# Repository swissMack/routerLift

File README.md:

# routerLift

Open-firmware automated router lift for a workshop router table. A 4.3" touch
panel with a CNC-style handwheel drives a stepper-actuated lift body, with
motion handled by stock [FluidNC](https://github.com/bdring/FluidNC).

Specification: `docs/Router_Lift_Requirement_Specification_RevG.md`, amended by
the Rev H design set.

## Architecture — two boards

Motion and the operator interface run on separate controllers. FluidNC does not
run on the ESP32-S3, and the S3 board cannot carry the machine's full pin
budget, so one board cannot do both.

```
  ESP32-S3 touch panel                 classic ESP32
  ┌──────────────────┐   UART/GRBL   ┌──────────────────┐
  │  hmi/  (our C++) │ ────────────► │ stock FluidNC    │   TB6600 ─► stepper
  │  LVGL, handwheel │ ◄──────────── │ firmware/*.yaml  │   NPN limits, probe
  └──────────────────┘  status @10Hz └──────────────────┘   relay ─► router
```

The HMI polls status with `?` every 100 ms — FluidNC's automatic report only
fires on change. No status for 500 ms counts as link loss: the HMI sends a feed
hold and invalidates Z0.

**The HMI has no motion authority.** Soft limits, hard limits, homing and
probing are all enforced by FluidNC. A bug in our firmware can produce a *wrong
cutting depth*; it must never produce an *unsafe move*. Keeping FluidNC stock
means the safety-critical parts are not ours to get wrong — any proposal that
needs FluidNC source edits forfeits that.

| Directory | Contents |
| --- | --- |
| `firmware/` | FluidNC machine definition — `config.yaml` only, **no source** |
| `hmi/` | PlatformIO ESP32-S3 project: LVGL UI, handwheel, buttons, GRBL sender |
| `legacy/` | The retired v1.x single-ESP32 firmware. Reference only, not built |
| `docs/` | Spec, Rev H design set, wiring, protocol, bench tests, mechanics |

## Hardware

**Motion board** — classic ESP32 (30-pin USB-C ESP32-WROOM-32 devkit) running
unmodified FluidNC v4.1.0. TB6600 driver at 1/8 microstepping (1600 pulse/rev),
24–36 V, common anode +3.3 V, 1.0–1.4 A/phase. NPN NC inductive limit switches,
`G38.2` probe for tool zeroing, `Relay` spindle output for router power with a
2500 ms spin-up gate. Host lift: sauter FML-P (1.5 mm lead, 65 mm travel).

**Operator panel** — Guition JC4827W543C board (XH-S3E N4R8 module: ESP32-S3,
4 MB flash, 8 MB octal PSRAM). 4.3" 480×272 IPS NV3041A panel over QSPI via
Arduino_GFX, GT911 capacitive touch, LVGL 8.4. The board brings only ten GPIOs
out to connectors, so the panel buttons and the rough/fine selector sit on an
MCP23017 on its own I²C bus (GPIO 15/16) — the touch bus is not brought out.
MPG handwheel decoded on the S3's PCNT peripheral (GPIO 6/7), through a 74LVC14
on 3.3 V (two stages per channel, non-inverting).

STOP is deliberately *not* on the panel: it is wired to FluidNC's own
`feed_hold_pin`, so it halts motion even if the HMI has crashed.

Full pin map and wiring: `docs/HARDWARE.md`, `docs/WIRING-RevH.svg`,
`docs/SCHEMATIC-RevH.svg`, `docs/PINOUT.svg`.

## Status

Bench truth lives in `docs/BRINGUP-LOG.md`. As of 2026-09-13:

| Half | State |
| --- | --- |
| Motion board | ✅ FluidNC v4.1.0 flashed, `config.yaml` parses, bare-board acceptance passed (limits NC-correct). Five items still to verify — `firmware/README.md` |
| Screen board | ✅ Display and touch working on the JC4827W543C |
| UART link (Step B) | ✅ Link up, link-loss feed hold + Z0 invalidation, recovery verified |
| `hmi/` increments 1–3 | Built. Display, touch and link bench-verified; MPG and buttons **not yet wired** (waiting on the level shifters) |
| `hmi/` increment 4 | Cycles (standard → bit-change → dovetail → keyhole). Not started |
| `hmi/` increment 5 | Fault log, diagnostics, runtime hours. Not started |
| Mechanics | Lift body (sauter FML-P) **not yet bought**. See `docs/MECHANICS-RevH.md` |

HMI flash use is ~24% of the 3 MB app slot.

### Nothing has been cut yet

Two numbers come from the sauter FML-P datasheet, not a measurement, and both
follow from its 1.5 mm screw lead:

- `firmware/config.yaml` → `steps_per_mm: 1066.67` (1600 pulse/rev ÷ 1.5 mm),
  with `max_travel_mm: 65`
- `hmi/include/config.h` → `MpgCfg::SCREW_LEAD_MM = 1.5`

**Until `steps_per_mm` is measured against a dial indicator, every depth this
machine cuts is wrong by an unknown factor** — and wrong invisibly, because
there is no stall detection to contradict a bad number. The commissioning
procedure is in `firmware/README.md`.

One design question is also open: the foot switch needs both press and release
edges for dead-man behaviour, and FluidNC's `macro0_pin` may only fire on
assert. The proposed split (press on FluidNC, release mirrored to an HMI
expander input) is written up in `firmware/README.md` and not yet verified.

## Build

Only the HMI is built from this repo. FluidNC is flashed from its own release.

```sh
git clone git@github.com:swissMack/routerLift.git
cd routerLift
pio run -e hmi           # compile
pio run -e hmi -t upload # flash the S3 panel
pio run -e hmi-diag      # bring-up diagnostics build (no I2C, display logging)
pio device monitor       # serial console at 115200
```

Libraries resolve on first build: ESP32Encoder, GFX Library for Arduino, LVGL
8.4, TAMC_GT911. If upload cannot connect because the app has hung, hold BOOT,
tap RST and retry.

For the motion board, flash stock FluidNC from installer.fluidnc.com, upload
`firmware/config.yaml` with `$Xmodem/Receive=/localfs/config.yaml`, and restart
with `$Bye` — see `firmware/README.md`. Its console is also reachable over WiFi:
`telnet routerlift.local 23`.

## Documentation

| File | Contents |
| --- | --- |
| [docs/Router_Lift_Requirement_Specification_RevG.md](docs/Router_Lift_Requirement_Specification_RevG.md) | The requirement spec |
| [docs/DESIGN-PLAN-RevH.md](docs/DESIGN-PLAN-RevH.md) | The RevG pivot, phase by phase |
| [docs/UART-PROTOCOL.md](docs/UART-PROTOCOL.md) | HMI ↔ FluidNC command vocabulary |
| [docs/MECHANICS-RevH.md](docs/MECHANICS-RevH.md) | Lift body selection and stepper drive design |
| [docs/LIFT-COMPARISON.md](docs/LIFT-COMPARISON.md) | The four candidate lift bodies, compared |
| [docs/BOM.md](docs/BOM.md) | Bill of materials |
| [docs/HARDWARE.md](docs/HARDWARE.md) | Pin map and wiring detail |
| [docs/BENCH-TEST.md](docs/BENCH-TEST.md) | Staged bring-up — each step passes before the next part is fitted |
| [docs/BRINGUP-LOG.md](docs/BRINGUP-LOG.md) | What has actually been proven on the bench, session by session |
| [docs/UX.md](docs/UX.md) | Interaction model |
| [docs/DESIGN-QA.md](docs/DESIGN-QA.md) | The design Q&A that settled the constants |
| [hmi/README.md](hmi/README.md) | HMI modules, build gotchas, Z0 validity rules |
| [firmware/README.md](firmware/README.md) | FluidNC setup, pre-power-up checks, commissioning |
| [CHANGELOG.md](CHANGELOG.md) | Version history |
| [CONTRIBUTING.md](CONTRIBUTING.md) | Code style, commit conventions |

`docs/SUPERSEDED.md` lists the drawings the Rev H set replaced.
`docs/reference/FXBB-original/` holds the FXBB FräsLift V3 documentation this
project draws on.

## Safety

This machine drives a high-RPM router. Read `firmware/README.md` before first
power-up — five of its checks are destructive or silently wrong if got wrong,
including PSU voltage (48 V destroys the TB6600), TB6600 common anode at 3.3 V
not 5 V, and NPN-not-PNP limit sensors.

Z0 — the reference every cut depth is measured from — is owned entirely by the
HMI, and **there is no override anywhere** on probe validity. That is
deliberate: a wrong reference does not fail visibly, it produces a
plausible-looking cut at the wrong depth. See `hmi/README.md`.

The author accepts no liability for misuse. Test with the router unpowered
first.

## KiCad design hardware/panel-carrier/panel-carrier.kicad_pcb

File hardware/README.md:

# Hardware — KiCad schematics (Rev H)

Generated from Python. **Do not edit the `.kicad_sch` files in KiCad** — the next
regeneration overwrites them. Change `tools/*.py` and run:

    hardware/tools/verify.sh     # tests, generate, ERC, PDFs, pin cross-check

After running `verify.sh`, restore unchanged PDFs with `git checkout -- hardware/*/*.pdf` unless the schematics actually changed.

| Project | What | For layout? |
| --- | --- | --- |
| `motion-carrier/` | ESP32 devkit sockets, 5 input conditioners, field terminals, link header | Yes |
| `panel-carrier/` | 74LVC14 MPG shifter, MCP23017 + pull-ups, MX1.25 leads to the display | Yes |
| `system/` | Mains, E-stop, PSU, modules and cabling between them | No — reference |

`tools/check_pins.py` fails if a schematic pin disagrees with `firmware/config.yaml` or
`hmi/include/pins.h`.

## PCBs

Boards are generated once, then **the routed `.kicad_pcb` is the source** — edit it in KiCad's PCB
Editor freely. Rebuilding from scratch overwrites hand edits:

    hardware/tools/get_freerouting.sh                                   # once
    /Applications/KiCad/KiCad.app/Contents/Frameworks/Python.framework/Versions/Current/bin/python3 \
      hardware/tools/gen_pcb.py motion-carrier                          # or panel-carrier

`get_freerouting.sh` fetches v2.1.0, which runs on Java 21. `gen_pcb.py` uses only the jar for
that pinned version (`hardware/tools/.cache/freerouting-2.1.0.jar`) and stops with an error if it
is missing. To try another version, delete the cached jar first, then run e.g.
`FREEROUTING_VERSION=v2.4.1 hardware/tools/get_freerouting.sh` — and run `gen_pcb.py` with the same
`FREEROUTING_VERSION` set. v2.2 and later need Java 25.

**Regenerating a board is destructive.** It overwrites the `.kicad_pcb`, replaces the `board` and
`net_settings` sections of its `.kicad_pro` (design rules and net classes edited in the GUI are
discarded; other sections are kept), and rewrites the fab zip, the board PDF and the renders.

`verify.sh` and `gen_pcb.py` run DRC with schematic parity and `--severity-all`, so warnings fail
too. Autorouting gives a different result each run, so check DRC after every regeneration.
Fabrication zips for JLCPCB (2-layer, 1.6 mm, HASL) are in `<board>/fab/<board>-jlcpcb.zip`.

| Board | Size | Mounting |
| --- | --- | --- |
| motion carrier | 140 × 80 mm | 4× M3 for standard DIN-rail PCB clips |
| panel carrier | 80 × 62 mm | 4× M3 corners, standoffs |

Mounting hole centres, in mm from the board's top-left corner (x right, y down). Each board's holes
form a rectangle:

| Board | Holes (x, y) | Pitch (x × y) |
| --- | --- | --- |
| motion carrier | (4, 4), (93, 4), (4, 56.5), (93, 56.5) | 89 × 52.5 mm |
| panel carrier | (4, 4), (76, 4), (4, 58), (76, 58) | 72 × 54 mm |

## Open items shown on the drawings

- Contactor coil voltage (BOM block A).
- MPG output type — R3/R4 on the panel carrier are DNP until known.
- Foot-switch release mirror (MCP GPA6) — needs a second pedal contact or a shared-contact decision.
- ESP32 devkit row spacing assumed 25.4 mm — measure before ordering boards.
- DIN-rail clip hole spacing — check against the clips bought.

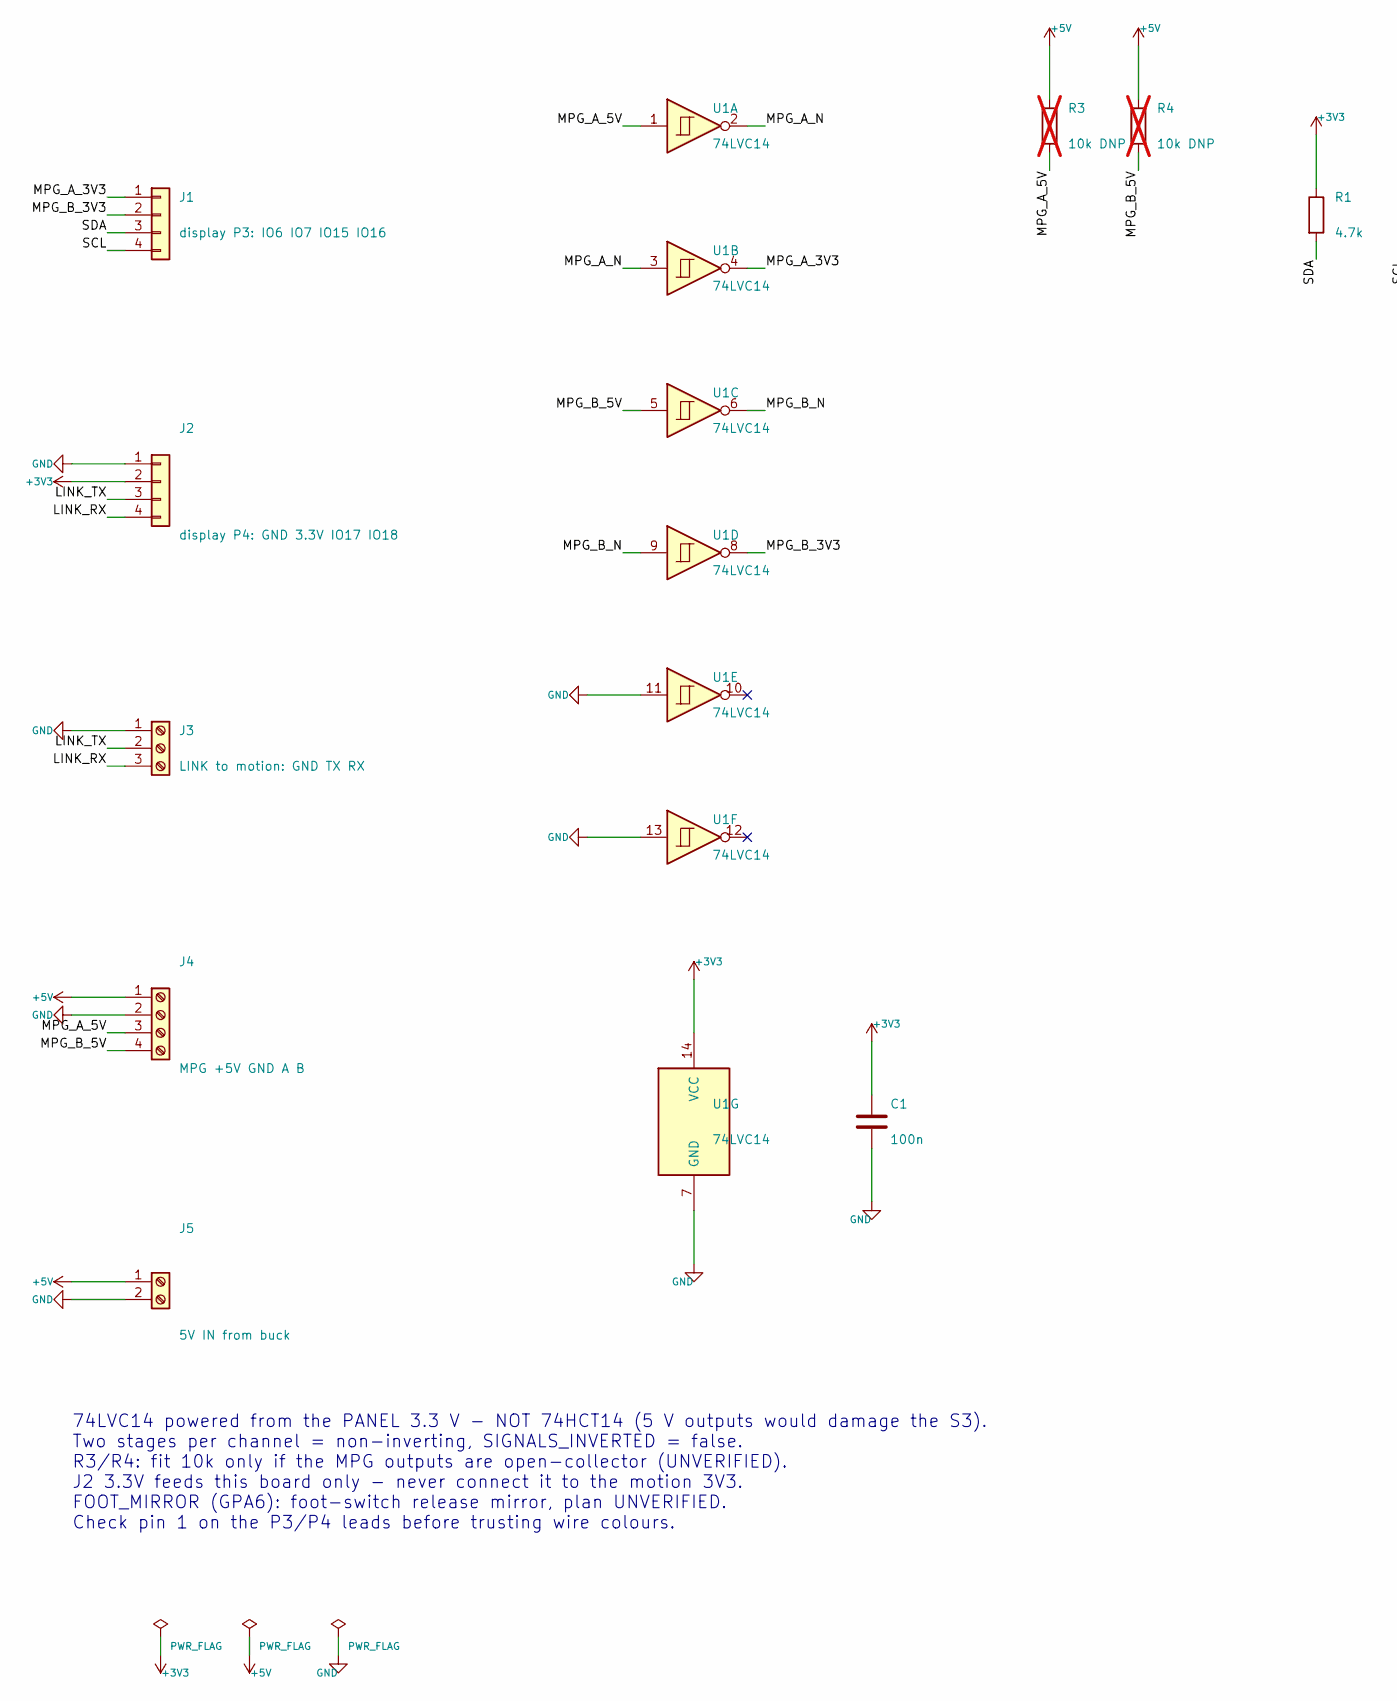
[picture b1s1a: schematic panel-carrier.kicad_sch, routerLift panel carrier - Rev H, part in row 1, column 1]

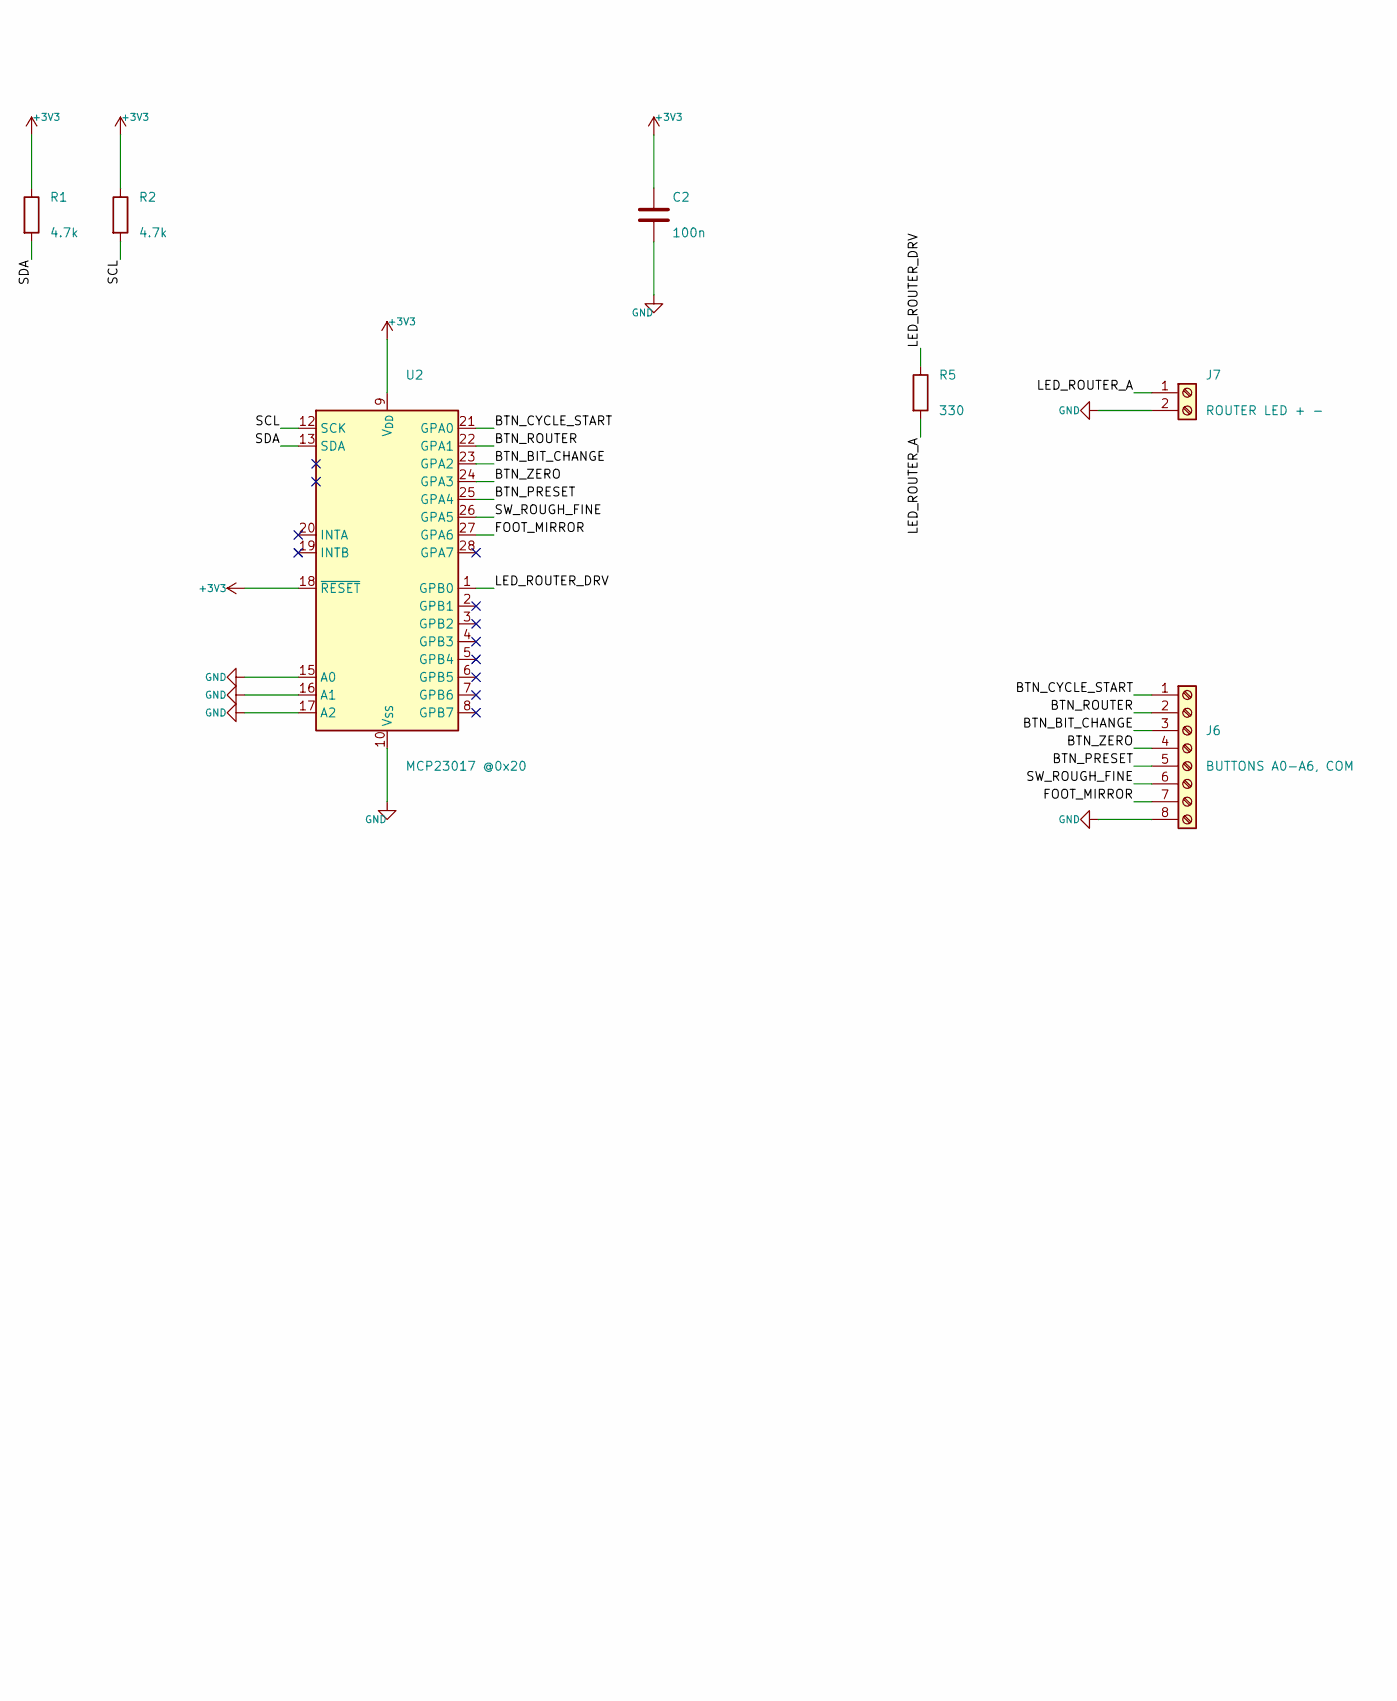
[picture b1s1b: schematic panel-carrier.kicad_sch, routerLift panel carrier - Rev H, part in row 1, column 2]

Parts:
C1, C2: 100n; C_Disc_D5.0mm_W2.5mm_P5.00mm
J1: display P3: IO6 IO7 IO15 IO16; Molex_PicoBlade_53047-0410_1x04_P1.25mm_Vertical
J2: display P4: GND 3.3V IO17 IO18; Molex_PicoBlade_53047-0410_1x04_P1.25mm_Vertical
J3: LINK to motion: GND TX RX; TerminalBlock_Phoenix_MKDS-1,5-3-5.08_1x03_P5.08mm_Horizont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
J4: MPG +5V GND A B; TerminalBlock_Phoenix_MKDS-1,5-4-5.08_1x04_P5.08mm_Horizont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
J5: 5V IN from buck; TerminalBlock_Phoenix_MKDS-1,5-2-5.08_1x02_P5.08mm_Horizont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
J6: BUTTONS A0-A6, COM; TerminalBlock_Phoenix_MKDS-1,5-8-5.08_1x08_P5.08mm_Horizont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
J7: ROUTER LED + -; TerminalBlock_Phoenix_MKDS-1,5-2-5.08_1x02_P5.08mm_Horizont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
R1, R2: 4.7k; R_Axial_DIN0207_L6.3mm_D2.5mm_P7.62mm_Horizontal
R3, R4: 10k DNP; R_Axial_DIN0207_L6.3mm_D2.5mm_P7.62mm_Horizontal; not fitted
R5: 330; R_Axial_DIN0207_L6.3mm_D2.5mm_P7.62mm_Horizontal
U1: 74LVC14; SOIC-14_3.9x8.7mm_P1.27mm
U2: MCP23017 @0x20; SOIC-28W_7.5x17.9mm_P1.27mm

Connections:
+3V3: C1.1, C2.1, J2.2, R1.1, R2.1, U1.14 (VCC), U2.9 (V_{DD}), U2.18 (~RESET)
+5V: J4.1, J5.1, R3.1, R4.1
/BTN_BIT_CHANGE: J6.3, U2.23 (GPA2)
/BTN_CYCLE_START: J6.1, U2.21 (GPA0)
/BTN_PRESET: J6.5, U2.25 (GPA4)
/BTN_ROUTER: J6.2, U2.22 (GPA1)
/BTN_ZERO: J6.4, U2.24 (GPA3)
/FOOT_MIRROR: J6.7, U2.27 (GPA6)
/LED_ROUTER_A: J7.1, R5.2
/LED_ROUTER_DRV: R5.1, U2.1 (GPB0)
/LINK_RX: J2.4, J3.3
/LINK_TX: J2.3, J3.2
/MPG_A_3V3: J1.1, U1.4
/MPG_A_5V: J4.3, R3.2, U1.1
/MPG_A_N: U1.2, U1.3
/MPG_B_3V3: J1.2, U1.8
/MPG_B_5V: J4.4, R4.2, U1.5
/MPG_B_N: U1.6, U1.9
/SCL: J1.4, R2.2, U2.12 (SCK)
/SDA: J1.3, R1.2, U2.13 (SDA)
/SW_ROUGH_FINE: J6.6, U2.26 (GPA5)
GND: C1.2, C2.2, J2.1, J3.1, J4.2, J5.2, J6.8, J7.2, U1.7 (GND), U1.11, U1.13, U2.10 (V_{SS}), U2.15 (A0), U2.16 (A1), U2.17 (A2)

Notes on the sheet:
74LVC14 powered from the PANEL 3.3 V - NOT 74HCT14 (5 V outputs would damage the S3). Two stages per channel = non-inverting, SIGNALS_INVERTED = false. R3/R4: fit 10k only if the MPG outputs are open-collector (UNVERIFIED). J2 3.3V feeds this board only - never connect it to the motion 3V3. FOOT_MI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

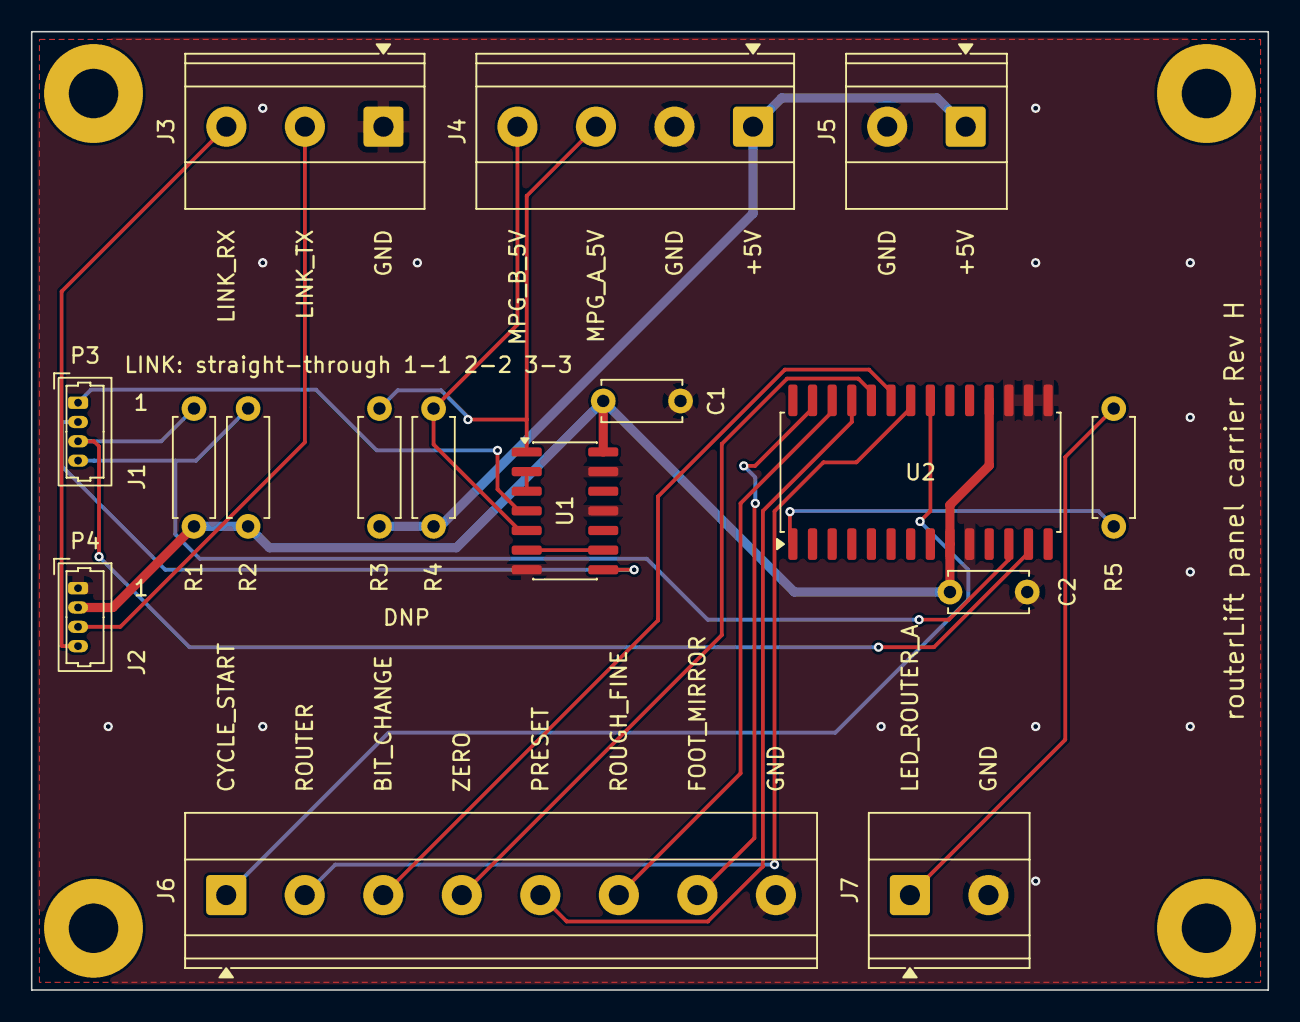
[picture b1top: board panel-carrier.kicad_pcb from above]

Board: 2 copper layers, 80.0 x 62.0 mm, 20 parts (0 on the bottom side), 22 nets.

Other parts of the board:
H1, H2, H3, H4: M3; MountingHole_3.2mm_M3_Pad

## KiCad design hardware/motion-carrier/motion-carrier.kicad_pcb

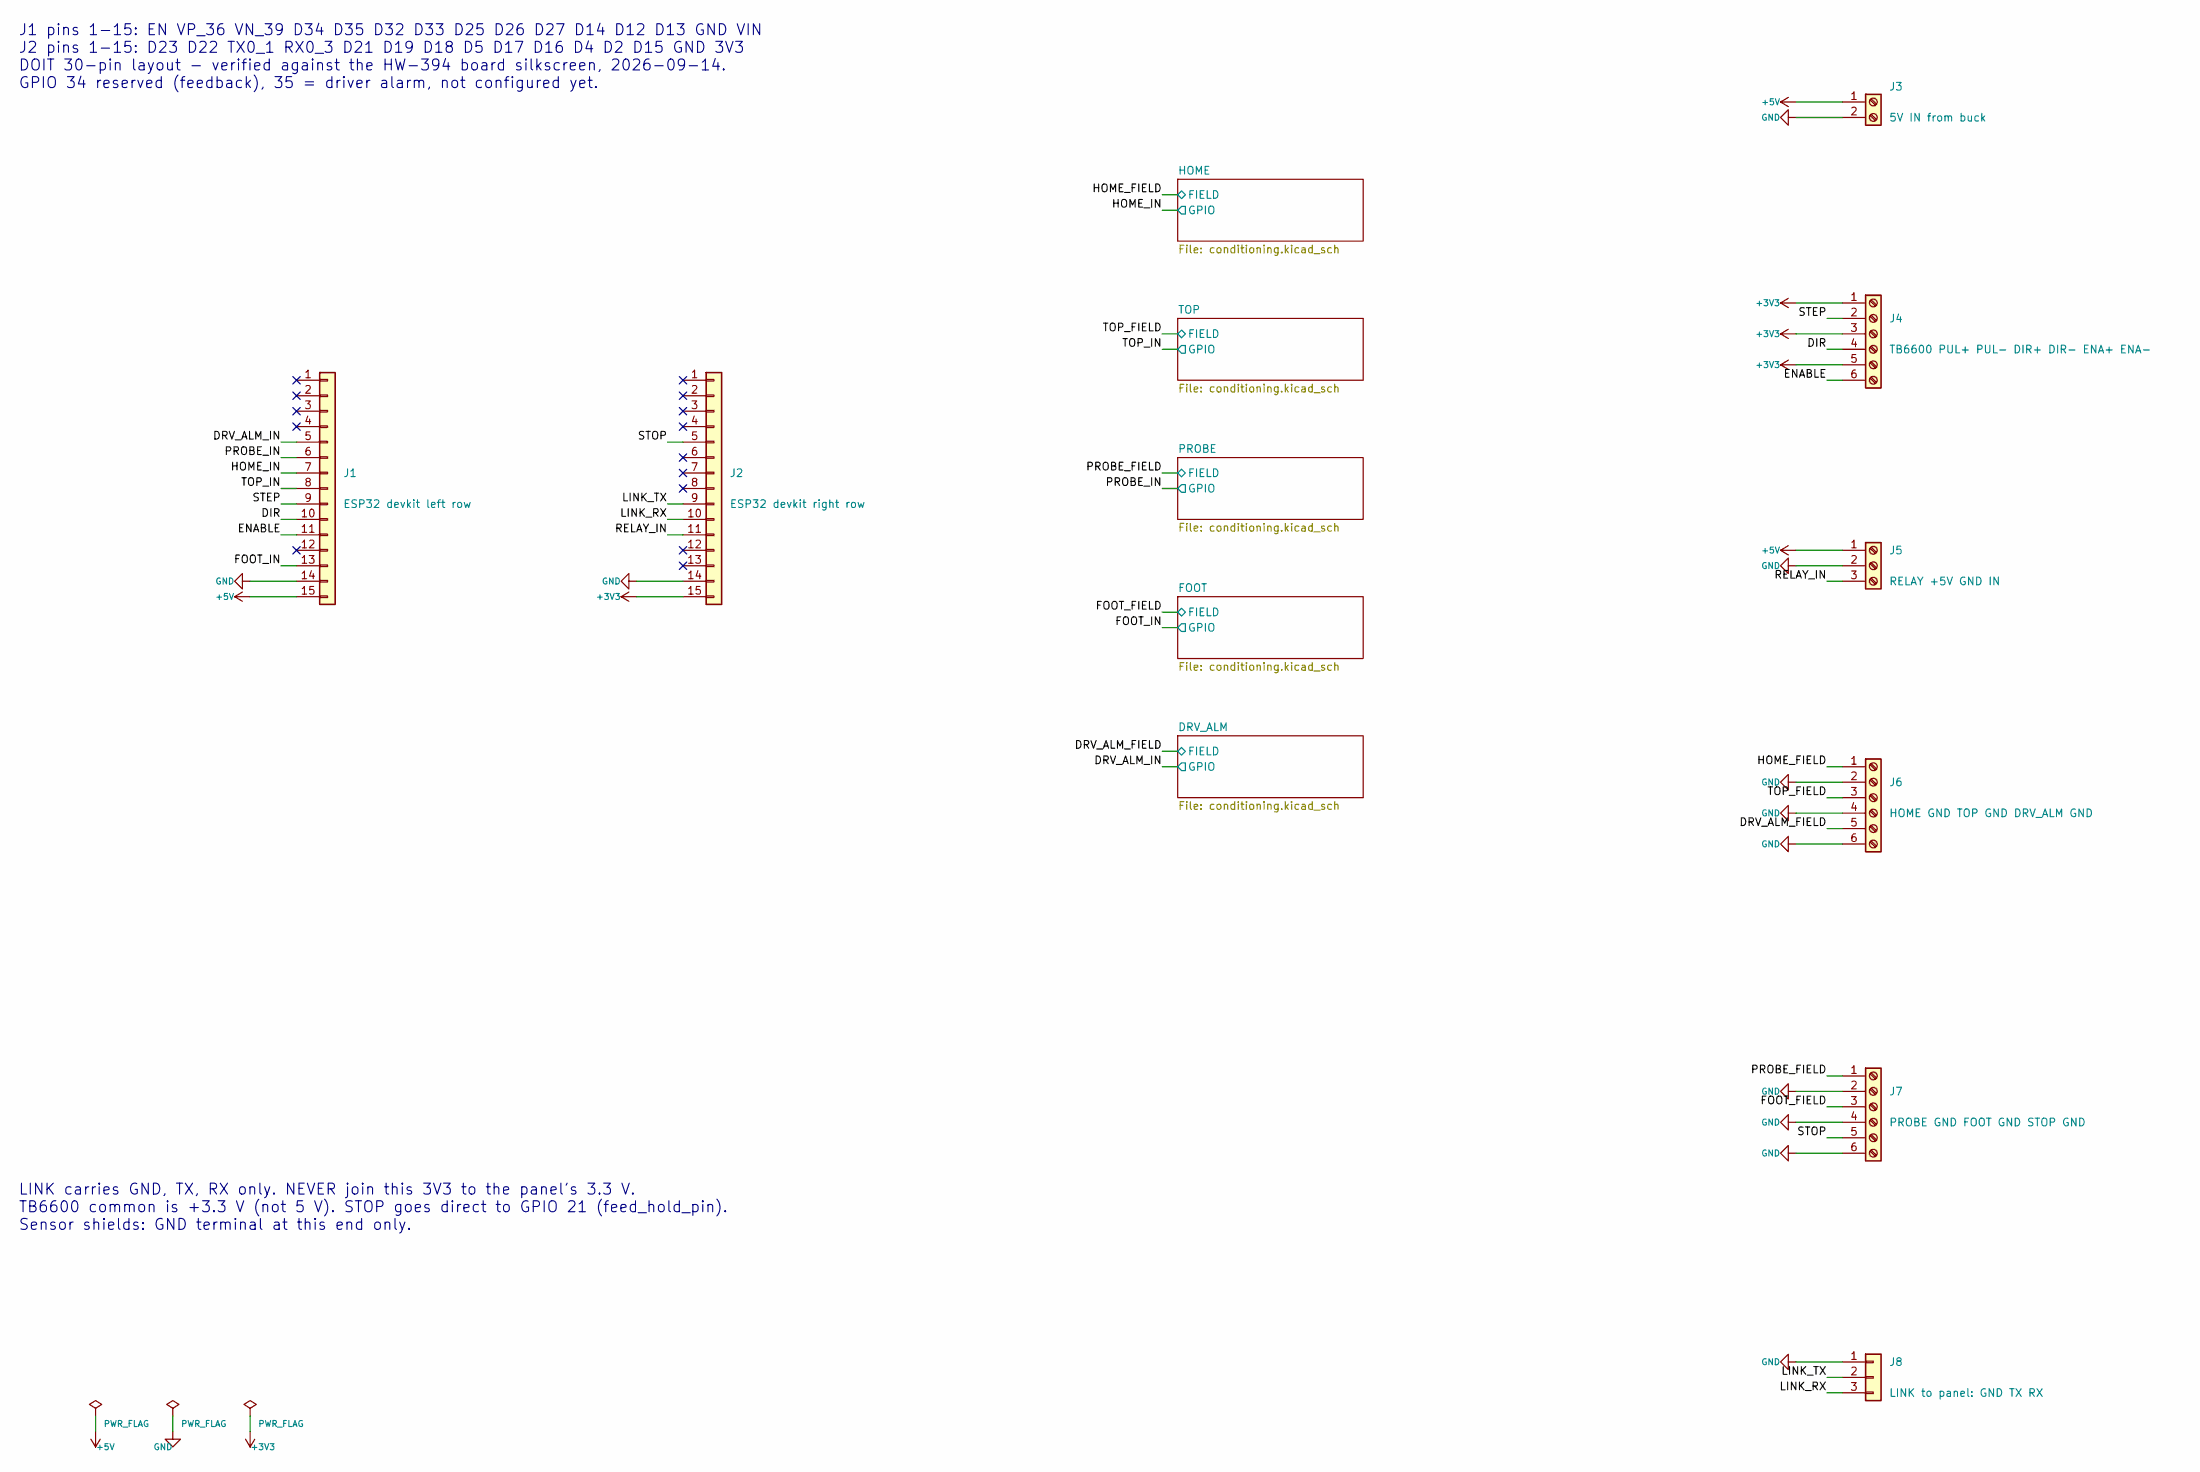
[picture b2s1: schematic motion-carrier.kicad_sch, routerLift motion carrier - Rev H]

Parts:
J1: ESP32 devkit left row; PinSocket_1x15_P2.54mm_Vertical
J2: ESP32 devkit right row; PinSocket_1x15_P2.54mm_Vertical
J3: 5V IN from buck; TerminalBlock_Phoenix_MKDS-1,5-2-5.08_1x02_P5.08mm_Horizont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
J4: TB6600 PUL+ PUL- DIR+ DIR- ENA+ ENA-; TerminalBlock_Phoenix_MKDS-1,5-6-5.08_1x06_P5.08mm_Horizont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
J5: RELAY +5V GND IN; TerminalBlock_Phoenix_MKDS-1,5-3-5.08_1x03_P5.08mm_Horizont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
J6: HOME GND TOP GND DRV_ALM GND; TerminalBlock_Phoenix_MKDS-1,5-6-5.08_1x06_P5.08mm_Horizont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
J7: PROBE GND FOOT GND STOP GND; TerminalBlock_Phoenix_MKDS-1,5-6-5.08_1x06_P5.08mm_Horizont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
J8: LINK to panel: GND TX RX; JST_XH_B3B-XH-A_1x03_P2.50mm_Vertical

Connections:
+3V3: J2.15, J4.1, J4.3, J4.5; also elsewhere on the board
+5V: J1.15, J3.1, J5.1
/DIR: J1.10, J4.4
/DRV_ALM_FIELD: J6.5; also elsewhere on the board
/DRV_ALM_IN: J1.5; also elsewhere on the board
/ENABLE: J1.11, J4.6
/FOOT_FIELD: J7.3; also elsewhere on the board
/FOOT_IN: J1.13; also elsewhere on the board
/HOME_FIELD: J6.1; also elsewhere on the board
/HOME_IN: J1.7; also elsewhere on the board
/LINK_RX: J2.10, J8.3
/LINK_TX: J2.9, J8.2
/PROBE_FIELD: J7.1; also elsewhere on the board
/PROBE_IN: J1.6; also elsewhere on the board
/RELAY_IN: J2.11, J5.3
/STEP: J1.9, J4.2
/STOP: J2.5, J7.5
/TOP_FIELD: J6.3; also elsewhere on the board
/TOP_IN: J1.8; also elsewhere on the board
GND: J1.14, J2.14, J3.2, J5.2, J6.2, J6.4, J6.6, J7.2, J7.4, J7.6, J8.1; also elsewhere on the board

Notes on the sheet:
J1 pins 1-15: EN VP_36 VN_39 D34 D35 D32 D33 D25 D26 D27 D14 D12 D13 GND VIN J2 pins 1-15: D23 D22 TX0_1 RX0_3 D21 D19 D18 D5 D17 D16 D4 D2 D15 GND 3V3 DOIT 30-pin layout - verified against the HW-394 board silkscreen, 2026-09-14. GPIO 34 reserved (feedback), 35 = driver alarm, not configured yet.
LINK carries GND, TX, RX only. NEVER join this 3V3 to the panel's 3.3 V. TB6600 common is +3.3 V (not 5 V). STOP goes direct to GPIO 21 (feed_hold_pin). Sensor shields: GND terminal at this end only.

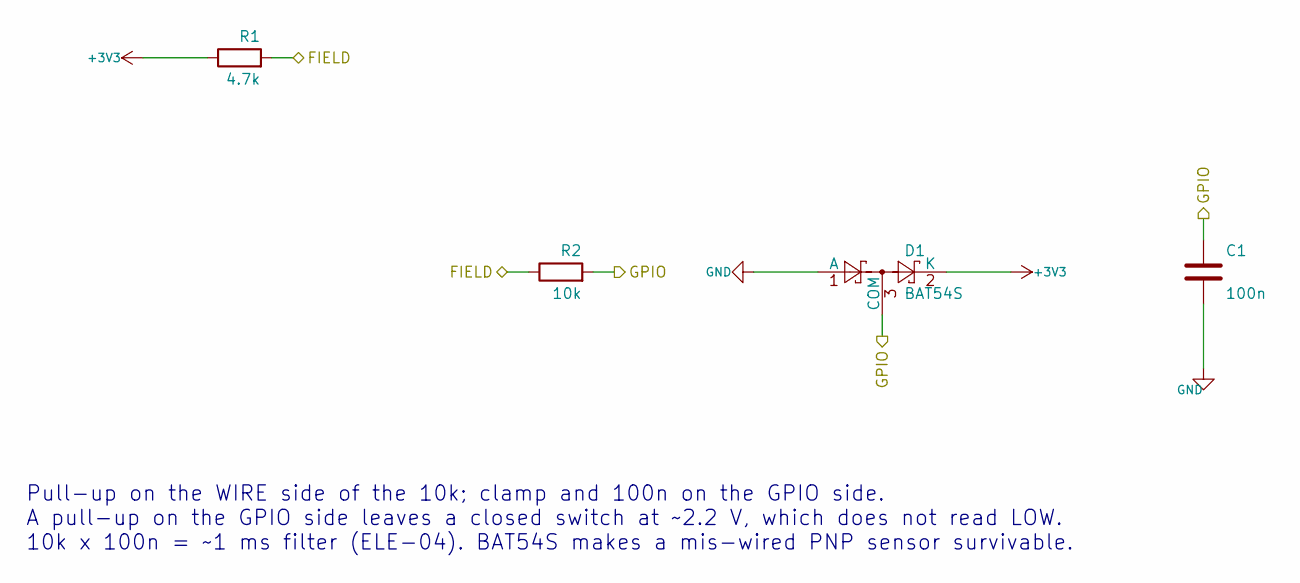
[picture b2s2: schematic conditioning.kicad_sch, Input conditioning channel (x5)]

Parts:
C1: 100n; C_Disc_D5.0mm_W2.5mm_P5.00mm
D1: BAT54S; SOT-23
R1: 4.7k; R_Axial_DIN0207_L6.3mm_D2.5mm_P7.62mm_Horizontal
R2: 10k; R_Axial_DIN0207_L6.3mm_D2.5mm_P7.62mm_Horizontal

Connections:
+3V3: D1.2 (K), R1.1; also elsewhere on the board
/HOME_FIELD: R1.2, R2.1; also elsewhere on the board
/HOME_IN: C1.1, D1.3 (COM), R2.2; also elsewhere on the board
GND: C1.2, D1.1 (A); also elsewhere on the board

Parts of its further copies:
C2, C3, C4, C5: 100n; C_Disc_D5.0mm_W2.5mm_P5.00mm
D2, D3, D4, D5: BAT54S; SOT-23
R3, R5, R7, R9: 4.7k; R_Axial_DIN0207_L6.3mm_D2.5mm_P7.62mm_Horizontal
R4, R6, R8, R10: 10k; R_Axial_DIN0207_L6.3mm_D2.5mm_P7.62mm_Horizontal

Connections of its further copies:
+3V3: D2.2 (K), D3.2 (K), D4.2 (K), D5.2 (K), R3.1, R5.1, R7.1, R9.1; also elsewhere on the board
/DRV_ALM_FIELD: R9.2, R10.1; also elsewhere on the board
/DRV_ALM_IN: C5.1, D5.3 (COM), R10.2; also elsewhere on the board
/FOOT_FIELD: R7.2, R8.1; also elsewhere on the board
/FOOT_IN: C4.1, D4.3 (COM), R8.2; also elsewhere on the board
/PROBE_FIELD: R5.2, R6.1; also elsewhere on the board
/PROBE_IN: C3.1, D3.3 (COM), R6.2; also elsewhere on the board
/TOP_FIELD: R3.2, R4.1; also elsewhere on the board
/TOP_IN: C2.1, D2.3 (COM), R4.2; also elsewhere on the board
GND: C2.2, C3.2, C4.2, C5.2, D2.1 (A), D3.1 (A), D4.1 (A), D5.1 (A); also elsewhere on the board

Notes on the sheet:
Pull-up on the WIRE side of the 10k; clamp and 100n on the GPIO side. A pull-up on the GPIO side leaves a closed switch at ~2.2 V, which does not read LOW. 10k x 100n = ~1 ms filter (ELE-04). BAT54S makes a mis-wired PNP sensor survivable.

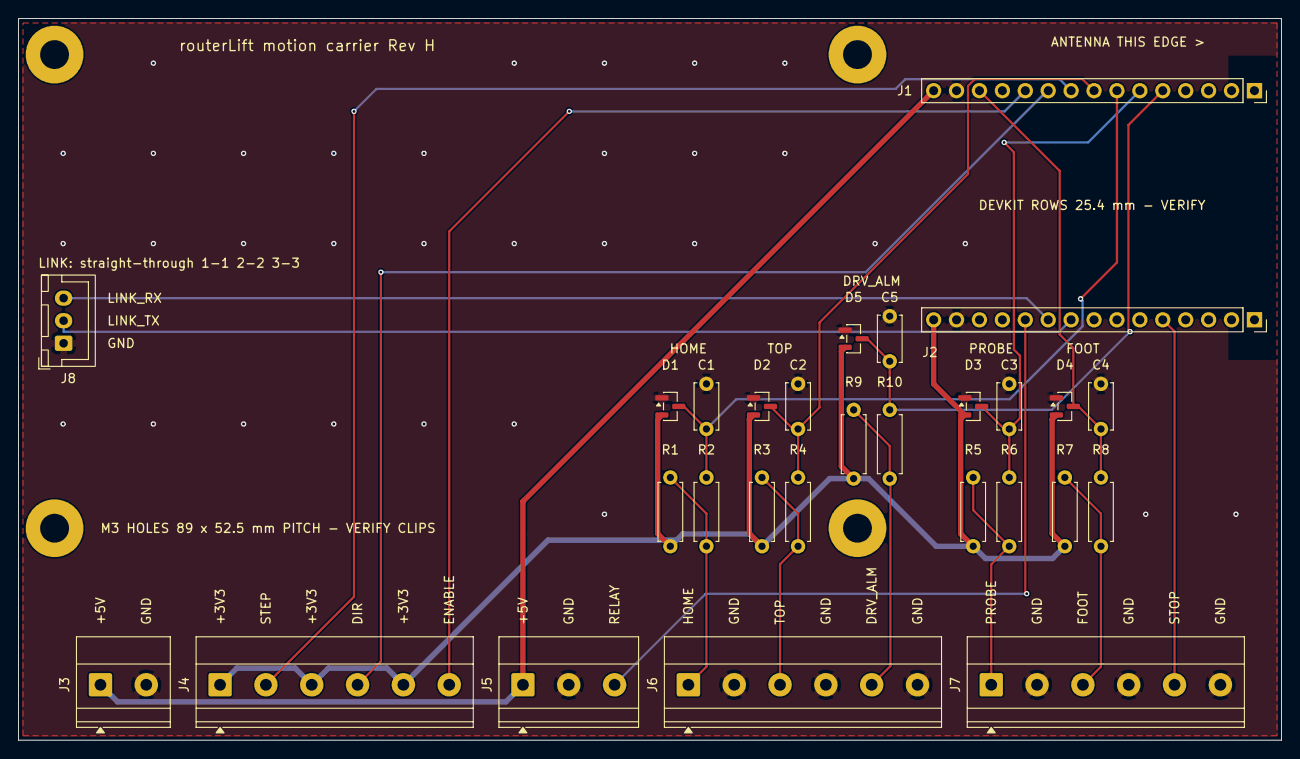
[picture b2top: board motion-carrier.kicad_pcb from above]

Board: 2 copper layers, 140.0 x 80.0 mm, 32 parts (0 on the bottom side), 20 nets.

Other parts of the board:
H1, H2, H3, H4: M3; MountingHole_3.2mm_M3_Pad

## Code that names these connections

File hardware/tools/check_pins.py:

"""Cross-check the carrier schematics against the firmware pin maps.

python3 hardware/tools/check_pins.py   (exit 0 = consistent)
"""
import os
import re
import subprocess
import sys
import tempfile
from pathlib import Path

sys.path.insert(0, str(Path(__file__).resolve().parent))
from devkit import DEVKIT_LEFT, DEVKIT_RIGHT, devkit_gpio
from kisch import find, findall, parse

KICAD_CLI = os.environ.get("KICAD_CLI", "/Applications/KiCad/KiCad.app/Contents/MacOS/kicad-cli")
HW = Path(__file__).resolve().parents[1]
REPO = HW.parent

MOTION_EXPECT = {
    ("uart1", "txd_pin"): "LINK_TX", ("uart1", "rxd_pin"): "LINK_RX",
    ("axes", "step_pin"): "STEP", ("axes", "direction_pin"): "DIR",
    ("axes", "disable_pin"): "ENABLE", ("axes", "limit_neg_pin"): "HOME_IN",
    ("axes", "limit_pos_pin"): "TOP_IN", ("probe", "pin"): "PROBE_IN",
    ("control", "feed_hold_pin"): "STOP", ("control", "macro0_pin"): "FOOT_IN",
    ("Relay", "output_pin"): "RELAY_IN",
}
RESERVED = {35: "DRV_ALM_IN"}
P3 = {"1": 6, "2": 7, "3": 15, "4": 16}
P4 = {"3": 17, "4": 18}
P4_POWER = {"1": "GND", "2": "+3V3"}
PANEL_EXPECT = {"MPG_A": "MPG_A_3V3", "MPG_B": "MPG_B_3V3", "MCP_SDA": "SDA", "MCP_SCL": "SCL",
                "UART_RX": "LINK_TX", "UART_TX": "LINK_RX"}
EXPANDER_EXPECT = {"A_CYCLE_START": "BTN_CYCLE_START", "A_ROUTER": "BTN_ROUTER",
                   "A_BIT_CHANGE": "BTN_BIT_CHANGE", "A_ZERO": "BTN_ZERO",
                   "A_PRESET": "BTN_PRESET", "A_ROUGH_FINE": "SW_ROUGH_FINE",
                   "A_FOOT_MIRROR": "FOOT_MIRROR", "B_ROUTER_LED": "LED_ROUTER_DRV"}
# GND, LINK_TX, LINK_RX in that pin order - motion-carrier J8 and panel-carrier J3 are
# the two ends of the same 3-wire link cable, so pin 1 on one end must be pin 1's net
# on the other, etc. (docs/WIRING-RevH.md, UART-PROTOCOL.md).
LINK_ORDER = ["GND", "LINK_TX", "LINK_RX"]
# GPA7 is the expander's only fully-spare button input (panel_carrier.py's mcp dict
# maps it to None -> a no-connect flag) - it must actually be unconnected in the
# schematic, not silently reused for something else.
EXPANDER_UNUSED = {"GPA7"}


def config_pins(text):
    section, out = None, {}
    for line in text.splitlines():
        if not line.strip() or line.lstrip().startswith("#"):
            continue
        m = re.match(r"^(\w+):", line)
        if m:
            section = m.group(1)
        m = re.match(r"^\s*(\w+):\s*gpio\.(\d+)", line)
        if m:
            key = (section, m.group(1))
            if key in out:
                raise ValueError("config.yaml: duplicate key %s.%s" % key)
            out[key] = int(m.group(2))
    return out


def header_constants(text):
    return {m.group(1): int(m.group(2)) for m in
            re.finditer(r"constexpr\s+\w+\s+(\w+)\s*=\s*(\d+)\s*;", text)}


def netlist(sch):
    with tempfile.TemporaryDirectory() as d:
        out = Path(d) / "net.net"
        subprocess.run([KICAD_CLI, "sch", "export", "netlist", "--format", "kicadsexpr",
                        "-o", str(out), str(sch)], check=True, capture_output=True)
        tree = parse(out.read_text(encoding="utf-8"))
    nodes = {}
    for net in findall(find(tree, "nets"), "net"):
        name = str(find(net, "name")[1]).split("/")[-1]
        for node in findall(net, "node"):
            pin = str(find(node, "pin")[1])
            func = find(node, "pinfunction")
            pinfunction = str(func[1]) if func else ""
            # kicad-cli's kicadsexpr netlist writes pinfunction as "<pin_name>_<pin_number>"
            # (confirmed by exporting a real netlist: MCP23017 pin 21 -> "GPA0_21", 74xx pin
            # 14 -> "VCC_14", a Conn_01x04 pin 1 -> "Pin_1_1") rather than the bare pin name -
            # strip the pin's own number back off so callers can match on the plain name.
            suffix = "_" + pin
            if pinfunction.endswith(suffix):
                pinfunction = pinfunction[: -len(suffix)]
            nodes[(str(find(node, "ref")[1]), pin)] = (name, pinfunction)
    return nodes


def check_motion(errors, nodes):
    gpio_net = {}
    for ref, row in (("J1", DEVKIT_LEFT), ("J2", DEVKIT_RIGHT)):
        for i, silk in enumerate(row):
            gpio = devkit_gpio(silk)
            if gpio is not None:
                gpio_net[gpio] = nodes[(ref, str(i + 1))][0]
    cfg = config_pins((REPO / "firmware" / "config.yaml").read_text(encoding="utf-8"))
    for key, net in MOTION_EXPECT.items():
        if key not in cfg:
            errors.append("config.yaml: %s.%s not found" % key)
        elif gpio_net.get(cfg[key]) != net:
            errors.append("config.yaml %s.%s = gpio.%d but the schematic has %r there, expected %r"
                          % (key[0], key[1], cfg[key], gpio_net.get(cfg[key]), net))
    used = set(cfg.values())
    for gpio, net in sorted(gpio_net.items()):
        if net.startswith("unconnected") or gpio in used:
            continue
        if RESERVED.get(gpio) != net:
            errors.append("GPIO %d carries %s but config.yaml does not use it" % (gpio, net))


def check_panel(errors, nodes):
    io_net = {io: nodes[("J1", pin)][0] for pin, io in P3.items()}
    io_net.update({io: nodes[("J2", pin)][0] for pin, io in P4.items()})
    consts = header_constants((REPO / "hmi" / "include" / "pins.h").read_text(encoding="utf-8"))
    for name, net in PANEL_EXPECT.items():
        if name not in consts:
            errors.append("pins.h: %s not found" % name)
        elif io_net.get(consts[name]) != net:
            errors.append("pins.h %s = %d but the schematic has %r there, expected %r"
                          % (name, consts[name], io_net.get(consts[name]), net))
    for pin, net in P4_POWER.items():
        actual = nodes.get(("J2", pin), (None, None))[0]
        if actual != net:
            errors.append("panel-carrier J2 (P4) pin %s is %r, expected %r"
                          % (pin, actual, net))
    mcp = {func: net for (ref, _), (net, func) in nodes.items() if ref == "U2"}
    for name, net in EXPANDER_EXPECT.items():
        if name not in consts:
            errors.append("pins.h: %s not found" % name)
            continue
        func = ("GPA%d" if name.startswith("A_") else "GPB%d") % consts[name]
        if mcp.get(func) != net:
            errors.append("pins.h %s -> %s but U2 %s is %r" % (name, net, func, mcp.get(func)))
    for func in EXPANDER_UNUSED:
        net = mcp.get(func)
        if net is None or not net.startswith("unconnected"):
            errors.append("U2 %s expected unconnected, has %r" % (func, net))


def check_link(errors, motion_nodes, panel_nodes):
    for i, expected in enumerate(LINK_ORDER, start=1):
        motion_net = motion_nodes.get(("J8", str(i)), (None, None))[0]
        panel_net = panel_nodes.get(("J3", str(i)), (None, None))[0]
        if motion_net != expected or panel_net != expected:
            errors.append(
                "link pin %d: motion-carrier J8 has %r, panel-carrier J3 has %r, both "
                "expected %r" % (i, motion_net, panel_net, expected))


def main():
    errors = []
    motion_nodes = netlist(HW / "motion-carrier" / "motion-carrier.kicad_sch")
    panel_nodes = netlist(HW / "panel-carrier" / "panel-carrier.kicad_sch")
    check_motion(errors, motion_nodes)
    check_panel(errors, panel_nodes)
    check_link(errors, motion_nodes, panel_nodes)
    for e in errors:
        print("MISMATCH:", e)
    print("check_pins: %d mismatch(es)" % len(errors))
    return 1 if errors else 0


if __name__ == "__main__":
    sys.exit(main())

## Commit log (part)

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2026-05-24 feat: v1.0.0 router lift firmware (ESP32, MPG, touch)
